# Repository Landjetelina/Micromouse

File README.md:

# Šnajderovi šamani
- Magdalena Grbavac
- Patrik Landeka
- Antea Parat

## Natjecanje: 
31.5. u Algebri -> [Lokacija na karti](https://maps.app.goo.gl/GhEoACbUTYHz3x7r8)

## Requirements:
- Kicad = hardware dizajn
- VScode -> eksetenzija MicroPico
- micro USB podatkovni kabel (stari punjač od mobitela koji podržava prenošenje podataka, a ne samo punjenje)

### Tips:
- klonirajte ovaj repo u VScode pa odmah imate pristup kodovima
- za updejt datoteke:

  ```
  1. git add .
  2. git commit -m "poruka koja ide s promjenom"
  3. git push origin main *ako javlja grešku prvo napraviti pull
  4. git pull origin main * po potrebi, preporučam da to bude prvi korak ako niste zadnji radili na projektu
  ```

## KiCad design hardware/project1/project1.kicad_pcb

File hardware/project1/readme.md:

zippano je preveliko pa moram ovako

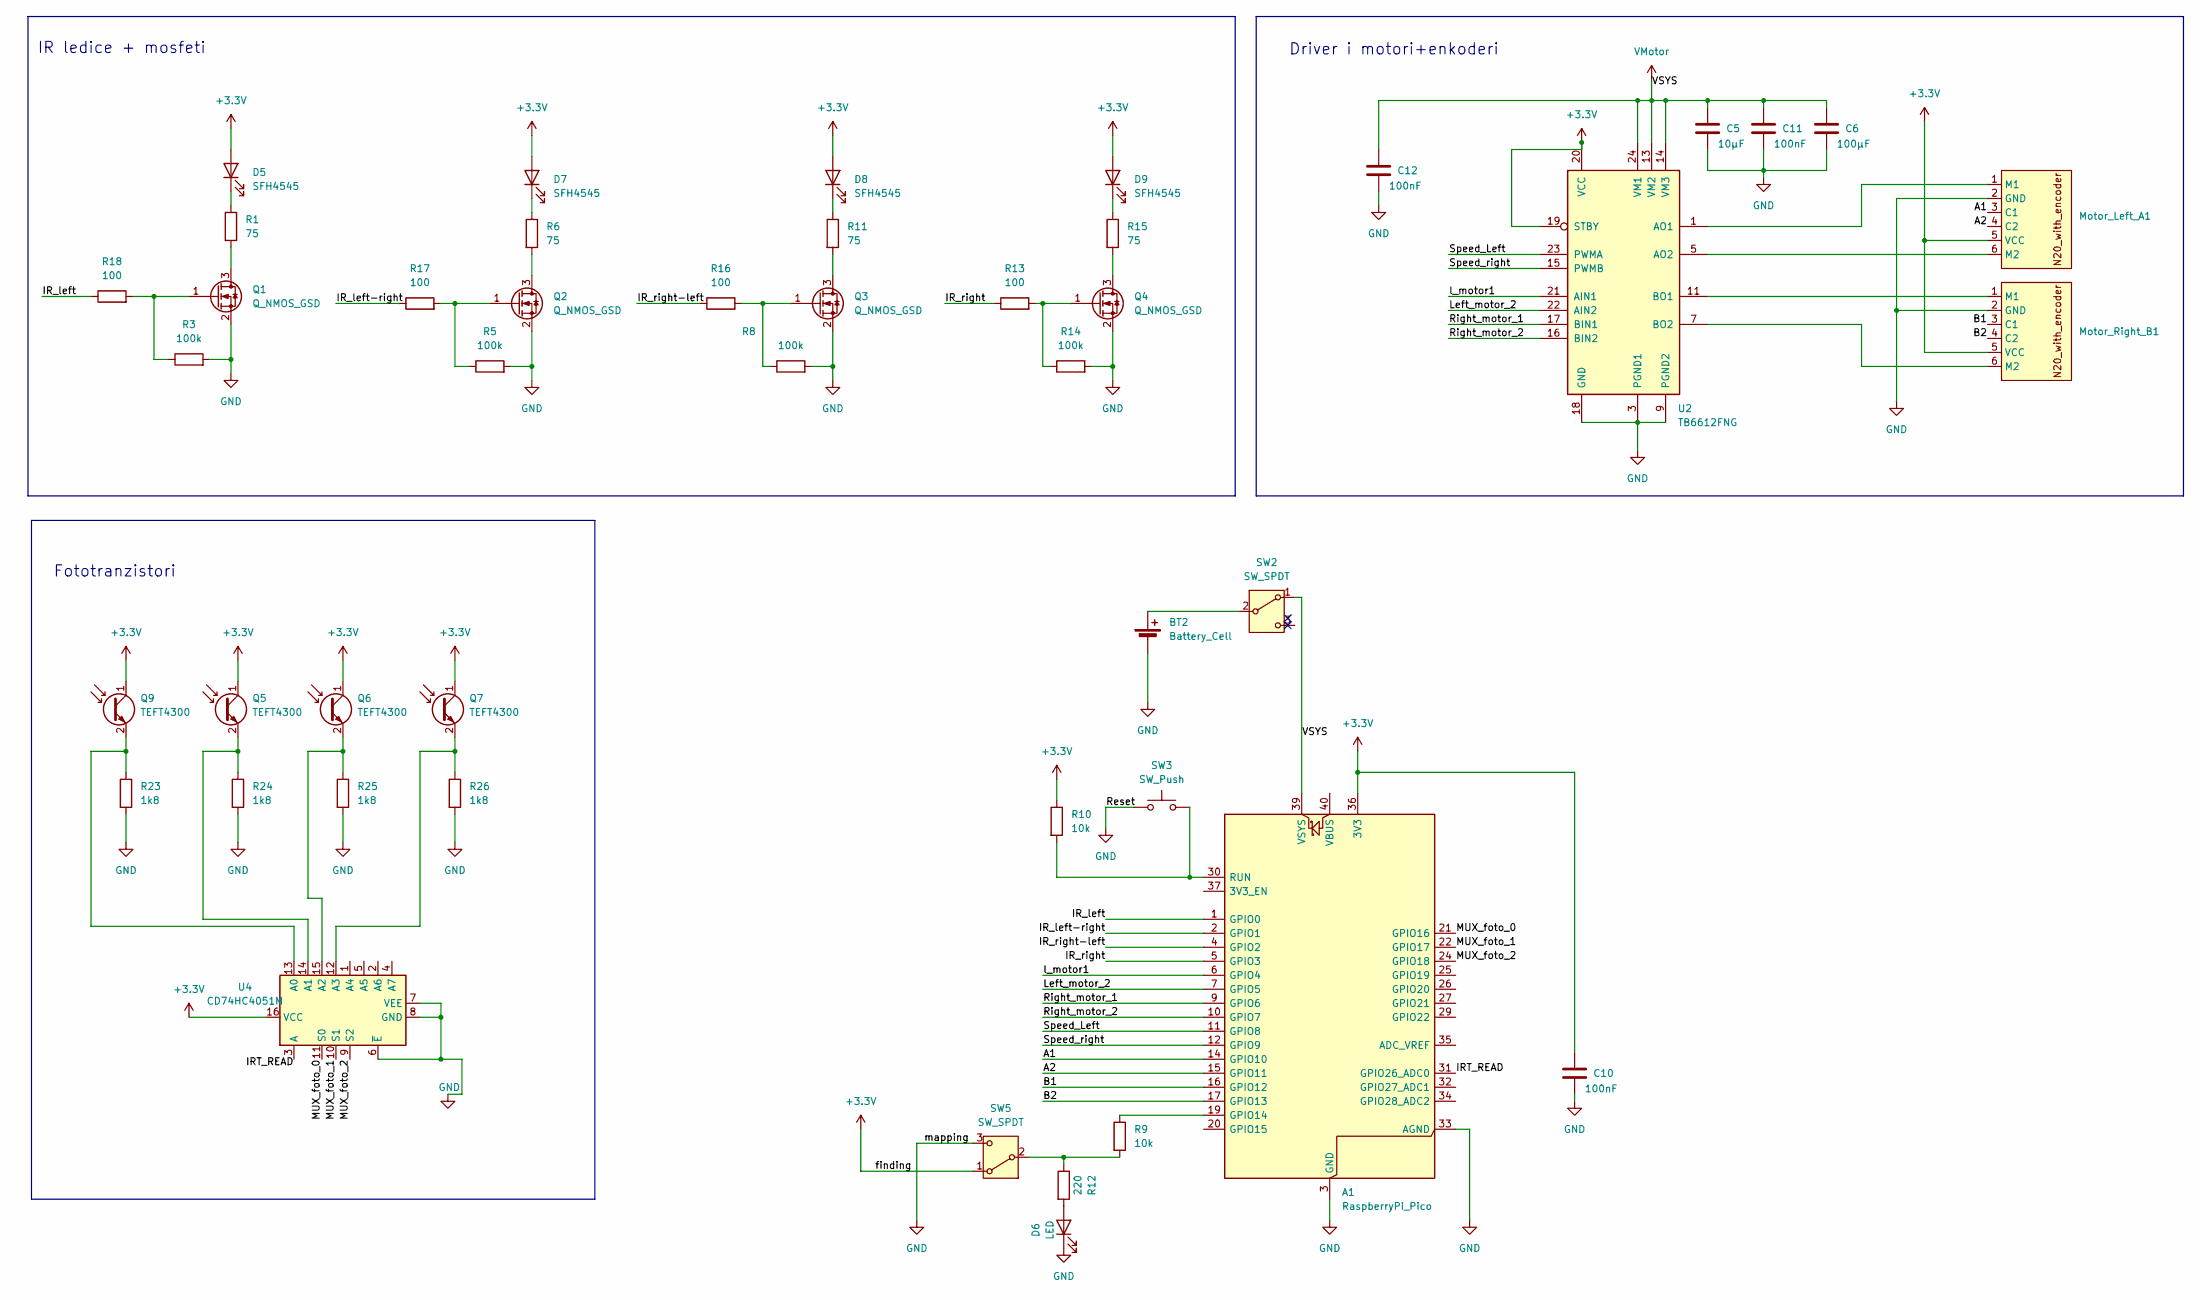
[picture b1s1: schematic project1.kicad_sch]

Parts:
A1: RaspberryPi_Pico; RaspberryPi_Pico_Common_Unspecified; MPN RP2040-PICO-HDR; Mouser 909-RP2040-PICO-HDR
BT2: Battery_Cell; JST_PH_B2B-PH-K_1x02_P2.00mm_Vertical; MPN B2B-PH-K-S(LF)(SN); Mouser 306-B2BPHKSLFSNPP
C5: 10µF; C_0603_1608Metric; MPN GRM188R60J106ME47D; Mouser 81-GRM188R60J106ME47
C6: 100µF; C_0805_2012Metric; MPN GRM21BR60G107ME1L; Mouser 81-GRM21BR60G107ME1L
C10, C11, C12: 100nF; C_0603_1608Metric; MPN GRM188R72A104KA35D; Mouser 81-GRM188R72A104KA35
D5, D7, D8, D9: SFH4545; LED_D5.0mm_Horizontal_O3.81mm_Z3.0mm; Manufacturer_Part_Number SFH 4545
D6: LED; LED_0805_2012Metric; MPN 604-APT1608CGCK; Mouser 604-APT1608CGCK
Motor_Left_A1: N20 DC Motor with Magnetic Encoder; PinHeader_1x06_P2.54mm_Vertical; MPN 4639; Mouser 485-4639
Motor_Right_B1: N20 DC Motor with Magnetic Encoder; PinHeader_1x06_P2.54mm_Vertical; MPN 4639; Mouser 485-4639
Q1, Q2, Q3, Q4: Q_NMOS_GSD; SOT-23; MPN SI2302CDS-T1-GE3; Mouser 781-SI2302CDS-T1-GE3
Q5, Q6, Q7, Q9: TEFT4300; LED_D3.0mm_Horizontal_O3.81mm_Z2.0mm; Manufacturer_Part_Number TEFT4300
R1, R6, R11, R15: 75; R_0805_2012Metric; MPN CRCW080568R0FKEA; Mouser 71-CRCW080568R0FKEA
R3, R5, R8, R14: 100k; R_0805_2012Metric; MPN CRCW0805100KFKEAC; Mouser 71-CRCW0805100KFKEAC
R9, R10: 10k; R_0805_2012Metric; MPN CRCW080510K0FKEAC; Mouser 71-CRCW080510K0FKEAC
R12: 220; R_0805_2012Metric; MPN CRCW0805220RFKEAC; Mouser 71-CRCW0805220RFKEAC
R13, R16, R17, R18: 100; R_0805_2012Metric; MPN CRCW0805100RFKEAC; Mouser 71-CRCW0805100RFKEAC
R23, R24, R25, R26: 1k8; R_0805_2012Metric; MPN CRCW08051K80FKEAC; Mouser 71-CRCW08051K80FKEAC
SW2, SW5: SW_SPDT; SW_SPDT_CK_JS102011SAQN; MPN JS102011SAQN; Mouser 611-JS102011SAQN
SW3: SW_Push; SW_PUSH_6mm; MPN TL1105SPF160Q; Mouser 612-TL1105SP
U2: TB6612FNG; SSOP-24_5.3x8.2mm_P0.65mm; MPN TB6612FNG,C,8,EL; Mouser 757-TB6612FNGC8EL
U4: CD74HC4051M; SOIC-16_4.55x10.3mm_P1.27mm; MPN CD74HC4051M96; Mouser 595-CD74HC4051M96

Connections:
+3.3V: A1.36 (3V3), C10.1, D5.2 (A), D7.2 (A), D8.2 (A), D9.2 (A), Motor_Left_A1.5 (VCC), Motor_Right_B1.5 (VCC), Q5.1 (C), Q6.1 (C), Q7.1 (C), Q9.1 (C), R10.1, SW5.1 (A), U2.19 (STBY), U2.20 (VCC), U4.16 (VCC)
/A1: A1.14 (GPIO10), Motor_Left_A1.3 (C1)
/A2: A1.15 (GPIO11), Motor_Left_A1.4 (C2)
/B1: A1.16 (GPIO12), Motor_Right_B1.3 (C1)
/B2: A1.17 (GPIO13), Motor_Right_B1.4 (C2)
/IRT_READ: A1.31 (GPIO26_ADC0), U4.3 (A)
/IR_left: A1.1 (GPIO0), R18.1
/IR_left-right: A1.2 (GPIO1), R17.1
/IR_right: A1.5 (GPIO3), R13.1
/IR_right-left: A1.4 (GPIO2), R16.1
/Left_motor_2: A1.7 (GPIO5), U2.22 (AIN2)
/MUX_foto_0: A1.21 (GPIO16), U4.11 (S0)
/MUX_foto_1: A1.22 (GPIO17), U4.10 (S1)
/MUX_foto_2: A1.24 (GPIO18), U4.9 (S2)
/Right_motor_1: A1.9 (GPIO6), U2.17 (BIN1)
/Right_motor_2: A1.10 (GPIO7), U2.16 (BIN2)
/Speed_Left: A1.11 (GPIO8), U2.23 (PWMA)
/Speed_right: A1.12 (GPIO9), U2.15 (PWMB)
/l_motor1: A1.6 (GPIO4), U2.21 (AIN1)
GND: A1.3 (GND), A1.8 (GND), A1.13 (GND), A1.18 (GND), A1.23 (GND), A1.28 (GND), A1.33 (AGND), A1.38 (GND), BT2.2 (-), C5.2, C6.2, C10.2, C11.2, C12.2, D6.1 (K), Motor_Left_A1.2 (GND), Motor_Right_B1.2 (GND), Q1.2 (S), Q2.2 (S), Q3.2 (S), Q4.2 (S), R3.2, R5.2, R8.2, R14.2, R23.2, R24.2, R25.2, R26.2, SW3.1, SW5.3 (C), U2.3 (PGND1), U2.4 (PGND1), U2.9 (PGND2), U2.10 (PGND2), U2.18 (GND), U4.6 (~E), U4.7 (VEE), U4.8 (GND)
unnamed: A1.19 (GPIO14), R9.1
unnamed: A1.30 (RUN), R10.2, SW3.2
unnamed: BT2.1 (+), SW2.2 (B)
unnamed: D5.1 (K), R1.1
unnamed: D6.2 (A), R12.2
unnamed: D7.1 (K), R6.1
unnamed: D8.1 (K), R11.1
unnamed: D9.1 (K), R15.1
unnamed: Motor_Left_A1.1 (M1), U2.1 (AO1), U2.2 (AO1)
unnamed: Motor_Left_A1.6 (M2), U2.5 (AO2), U2.6 (AO2)
unnamed: Motor_Right_B1.1 (M1), U2.11 (BO1), U2.12 (BO1)
unnamed: Motor_Right_B1.6 (M2), U2.7 (BO2), U2.8 (BO2)
unnamed: Q1.3 (D), R1.2
unnamed: Q1.1 (G), R3.1, R18.2
unnamed: Q2.3 (D), R6.2
unnamed: Q2.1 (G), R5.1, R17.2
unnamed: Q3.3 (D), R11.2
unnamed: Q3.1 (G), R8.1, R16.2
unnamed: Q4.3 (D), R15.2
unnamed: Q4.1 (G), R13.2, R14.1
unnamed: Q5.2 (E), R24.1, U4.14 (A1)
unnamed: Q6.2 (E), R25.1, U4.15 (A2)
unnamed: Q7.2 (E), R26.1, U4.12 (A3)
unnamed: Q9.2 (E), R23.1, U4.13 (A0)
unnamed: R9.2, R12.1, SW5.2 (B)
VMotor: A1.39 (VSYS), C5.1, C6.1, C11.1, C12.1, SW2.1 (A), U2.13 (VM2), U2.14 (VM3), U2.24 (VM1)

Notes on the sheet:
Driver i motori+enkoderi
IR ledice + mosfeti
Fototranzistori

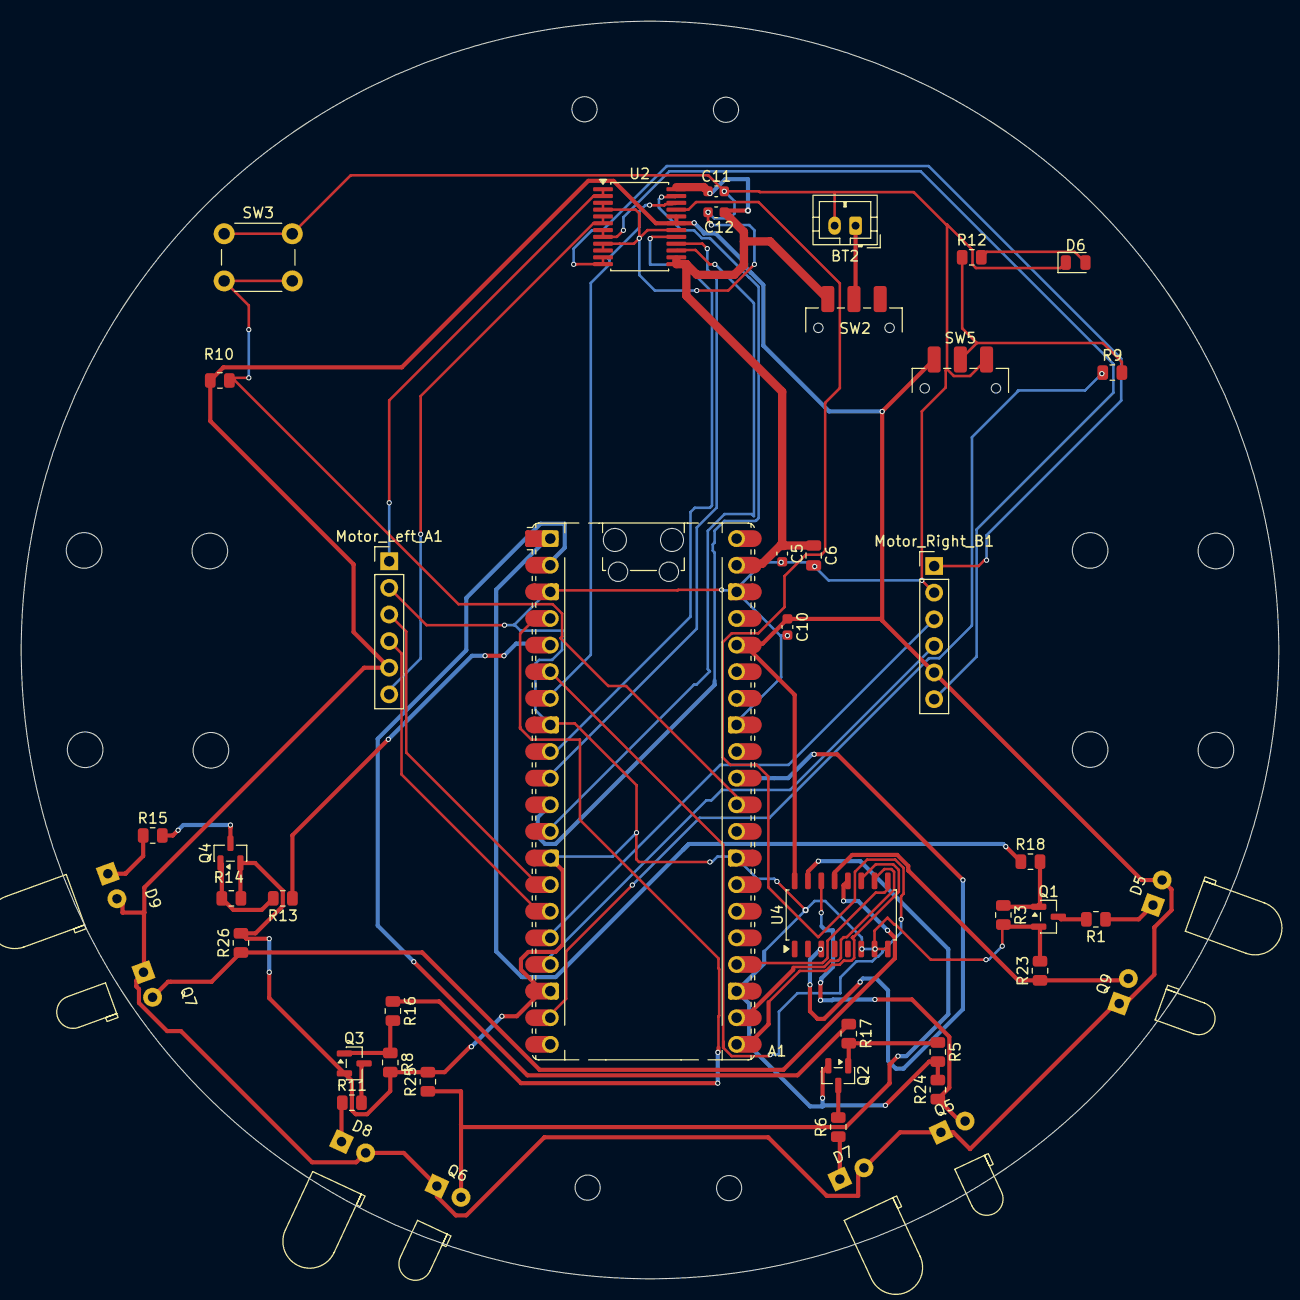
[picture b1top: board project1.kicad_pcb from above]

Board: 2 copper layers, 120.0 x 120.0 mm, 46 parts (0 on the bottom side), 46 nets.

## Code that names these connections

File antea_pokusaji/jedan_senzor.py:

from machine import Pin, ADC
import time

# Iz netliste: MUX select pinovi
mux_s = [
    Pin(16, Pin.OUT),  # MUX_foto_0 → GPIO16
    Pin(17, Pin.OUT),  # MUX_foto_1 → GPIO17
    Pin(18, Pin.OUT),  # MUX_foto_2 → GPIO18
]

# IR LED za kanal koji testiraš
# kanal 0 → IR_left (GPIO0), kanal 1 → IR_left-right (GPIO1), itd.
IR_LEDS = [
    Pin(0, Pin.OUT),   # IR_left
    Pin(1, Pin.OUT),   # IR_left-right
    Pin(2, Pin.OUT),   # IR_right-left
    Pin(3, Pin.OUT),   # IR_right
]

# ADC: IRT_READ → GPIO26
adc = ADC(Pin(26))

# SAMO TU MIJENJAJ OVE VARIJABLE
KANAL = 3   # 0–3, mijenjaj za testiranje
# 0 = IR_left (Q9) radi
# 1 = IR_left-right (Q5) radi
# 2 = IR_right-left (Q6) radi
# 3 = IR_right (Q7) radi
PRAG = 4000

def mux_odaberi(kanal):
    mux_s[0].value((kanal >> 0) & 1)
    mux_s[1].value((kanal >> 1) & 1)
    mux_s[2].value((kanal >> 2) & 1)


# optimalno je držati prag 3000-4000
# Upali samo IR LED za odabrani kanal
IR_LEDS[KANAL].value(1)
mux_odaberi(KANAL)

while True:
    time.sleep_us(50)
    vrijednost = adc.read_u16()
    prepreka = vrijednost > PRAG
    print(f"Kanal {KANAL}: {vrijednost} | {'PREPREKA' if prepreka else 'OK'}")
    time.sleep(0.1)

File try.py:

from machine import Pin, PWM, ADC
import time

# IR LED kontrola (pali emitere)
ir_led = [
    Pin(0, Pin.OUT),  # IR_left
    Pin(1, Pin.OUT),  # IR_left-right
    Pin(2, Pin.OUT),  # IR_right-left
    Pin(3, Pin.OUT),  # IR_right
]

# MUX select (odabir kojeg fototranzistora čitaš)
mux_s = [
    Pin(16, Pin.OUT),  # MUX_foto_0
    Pin(17, Pin.OUT),  # MUX_foto_1
    Pin(18, Pin.OUT),  # MUX_foto_2
]

# ADC za čitanje MUX izlaza
adc = ADC(Pin(26))  # IRT_READ

# Motor driver
left_motor_1  = Pin(4, Pin.OUT)
left_motor_2  = Pin(5, Pin.OUT)
right_motor_1 = Pin(6, Pin.OUT)
right_motor_2 = Pin(7, Pin.OUT)

speed_left  = PWM(Pin(8))
speed_right = PWM(Pin(9))
speed_left.freq(1000)           # frekvencija PWM signala (1 kHz je dobar izbor za motore)
speed_right.freq(1000)          # jer prevelika frekvencija može uzrokovati pregrijavanje motora, a premala može uzrokovati zujanje i neefikasno upravljanje brzinom

PRAG = 40000  # podesi eksperimentalno (0-65535) - vrijednost iznad koje se smatra da je prepreka detektirana

def mux_odaberi(kanal):
    # kanal 0-3 za 4 fototranzistora
    mux_s[0].value((kanal >> 0) & 1)
    mux_s[1].value((kanal >> 1) & 1)
    mux_s[2].value((kanal >> 2) & 1)  # treći bit = 0 za kanale 0-3

def citaj_senzor(kanal):
    mux_odaberi(kanal)
    time.sleep_us(50)           # kratka pauza da se MUX stabilizira
    return adc.read_u16()       # to je fototranz na gpio26, koji je povezan na MUX izlaz

#100 000 ne postoji — duty_u16 je 16-bitni, maksimum je 65535. Sve iznad toga se "wraparound" ili baca grešku, ne daje više brzine
def motori_naprijed(brzina=65535):
    left_motor_1.value(0)  
    left_motor_2.value(1)
      
    right_motor_1.value(1)
    right_motor_2.value(0)
    speed_left.duty_u16(brzina)
    speed_right.duty_u16(brzina)

def motori_stop():
    left_motor_1.value(0); left_motor_2.value(0)
    right_motor_1.value(0); right_motor_2.value(0)
    speed_left.duty_u16(0)
    speed_right.duty_u16(0)

# Upali sve IR LEDs
for led in ir_led:
    led.value(1)

while True:
    ocitanja = [citaj_senzor(k) for k in range(4)]
    prepreka = any(v > PRAG for v in ocitanja)

    print(f"Senzori: {ocitanja} | {'STOP' if prepreka else 'OK'}")

    if prepreka:
        motori_stop()
    else:
        motori_naprijed()

    time.sleep(0.05)

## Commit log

2026-05-21 readme
2026-05-21 pokusaj prvi
2026-05-21 popravljen smjer
2026-05-21 jel popravljen mux?
2026-05-22 Add hardware documentation for Micromouse project
    Added detailed documentation for the Micromouse hardware, including components, pin assignments, schematics, IR sensor circuit, motor driver, and power supply information.
2026-05-22 verzija3_popravljeno_predano
    moram probati još zipani kicad projekt
2026-05-22 Add initial content to readme.md
2026-05-22 valjda je okej pushano
    skinite kao zip
2026-05-22 Revise hardware component descriptions in readme
    Updated the description of the TB6612FNG component and removed the TEFA4300 entry.
2026-05-22 Add readme for hardware datasheets
2026-05-22 Add firmware installation instructions for RPI Pico
    Added instructions for flashing firmware to RPI Pico.
2026-05-22 Update README with team members and competition info
2026-05-24 Update project1newest.csv with new component details
2026-05-25 updejt Antea
2026-05-25 malo rearange
2026-05-25 Update event date with location link
    Added location link for the event in README.
2026-05-25 Delete hardware/project1/project1.net
    stari netlist
2026-05-25 fresh netlist
2026-05-25 Fix spelling and add Git usage tips in README
    Corrected spelling of 'dizajn' and added tips for using Git.
2026-05-25 popravljeni senzori, probni program je main
    da bi pico samostalno pokrenuo program, navodno treba nazvati main
2026-05-25 dodane napomene
2026-05-28 Update readme with code organization details
    Added a section on code organization and clarified file purposes.
2026-05-28 Fix formatting in readme for Pico upload instructions
2026-05-28 Započeta kalibracija senzora, imao problema s importima nakon dodavanja machine.reset() sve puklo. Ne mogu se povezati sa micropico kontrolerom
2026-05-28 robot moze voziti ravno i staje blizu prepreke
2026-05-29 Dodana ir_lookup_table i napravljena kalibracija senzora za 1.5-5.0 cm
2026-05-30 Dodana funkcija za računanje koordinata na kojoj se prepreka nalazi iako ne radi baš dobro :(
2026-05-30 Dodana skica robota gdje sam računao kuteve i preračunavao udaljenosti u koordinate
2026-05-30 dodano skretanje koje ne radi
2026-05-30 Napravljen PID, robot radi kao na videu
2026-05-30 navigacija
